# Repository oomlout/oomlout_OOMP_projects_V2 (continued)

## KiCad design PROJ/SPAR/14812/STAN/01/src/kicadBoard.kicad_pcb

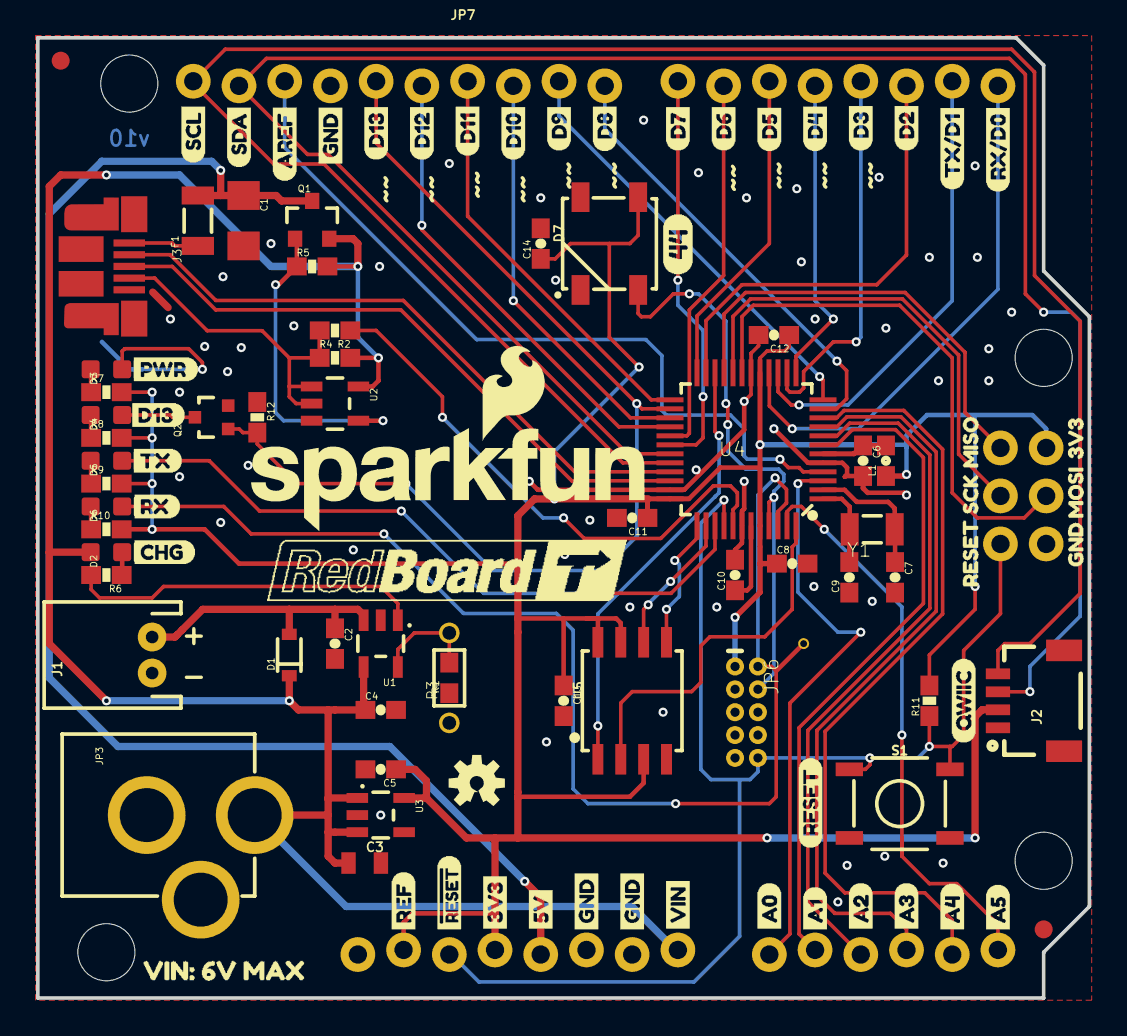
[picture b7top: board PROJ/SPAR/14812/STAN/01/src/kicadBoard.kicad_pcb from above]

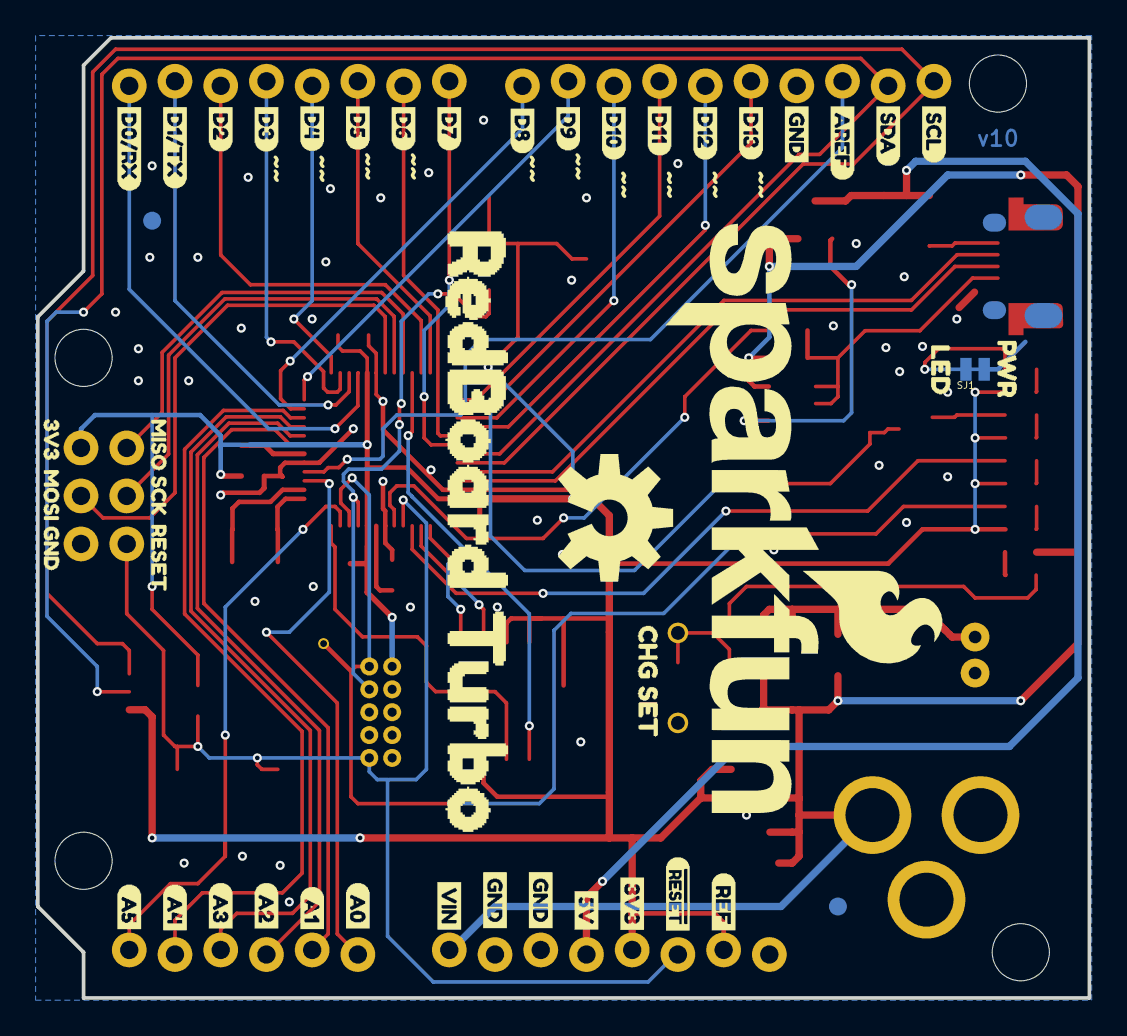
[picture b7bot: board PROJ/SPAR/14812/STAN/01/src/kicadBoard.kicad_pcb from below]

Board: 2 copper layers, 58.4 x 53.3 mm, 149 parts (46 on the bottom side), 58 nets.

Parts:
C1: 2.2UF; 1206@1
C2, C4: 4.7uF; 0603-CAP
C3: 1.0uF; 0805
C5: 2.2uF; 0603-CAP
C6, C8, C10, C11, C12, C13, C14: 0.1uF; 0603-CAP
C7, C9: 15pF; 0603-CAP
D1: BAT20J; SOD-323
D2, D6: Yellow; LED-0603
D3: RED; LED-0603
D4: BLUE; LED-0603
D5: GREEN; LED-0603
D7: WS2812B
F1: 500mA; PTC-1206
FID1, FID2, FID3, FID4: FIDUCIAL1X2; FIDUCIAL-1X2
FRAME1: FRAME-LEDGER; CREATIVE_COMMONS
J1: JST-2-PTH
J2: 1X04_1MM_RA
J3: USB-MICROB-PTH-MILL
JP3: POWER_JACKPTH; POWER_JACK_PTH
JP6: CORTEX_DEBUGPTH; 2X5-PTH-1.27MM
JP7: ARDUINO_UNO_R3LOCK_HOLES; ARDUINO_R3_LOCK_HOLES
L1: FB - 30Ohm; 0603
LOGO1: SFE_LOGO_NAME_FLAME.2_INCH; SFE_LOGO_NAME_FLAME_.2
LOGO2: SFE_LOGO_NAME_FLAME.3_INCH; SFE_LOGO_NAME_FLAME_.3
LOGO3: OSHW-LOGOS; OSHW-LOGO-S
LOGO4: OSHW-LOGOL; OSHW-LOGO-L
Q1: 2.5A/30V; SOT23-3
Q2: 2N7002PW; SOT323
R1: 3.9K; 0603
R2, R6, R7, R8, R9, R10: 330; 0603-RES
R3: PROG; 1_6W-RES
R4, R12: 100k; 0603-RES
R5: 47K; 0603-RES
R11: 10K; 0603-RES
S1: TACTILE_SWITCH_SMD_5.2MM
SJ1: PWR-LED; PAD-JUMPER-2-NC_BY_TRACE_NO_SILK
TP1: TEST-POINTTP_15TH_THRU; TP_15TH
U1: MCP73831; SOT23-5
U2: 74AHC1G125; SOT23-5
U3: 3.3V; SOT23-5
U4: ATSAMD21G-A; TQFP-48
U5: W25Q32FV; SOIC-8
U$1, U$44: #RESET1
U$2: 3V317
U$3: 5V18
U$4: CHG30
U$5: RX#D015
U$6: TX#D114
U$7: D213
U$8: D312
U$9: D411
U$10: D510
U$11: D69
U$12: D78
U$13: D87
U$14: D96
U$15: D105
U$16: D114
U$17: D123
U$18: D132
U$19, U$36, U$37: GND16
U$20, U$81: SDA1
U$21, U$80: SCL0
U$22: TX28
U$23: RX29
U$24: PWR26
U$25: D1327
U$26: REF0
U$27, U$53: AREF2
U$28: QWIIC31
U$29: A020
U$30: A121
U$31: A222
U$32: A323
U$33: A424
U$34: A525
U$35: VIN19
U$38: GND7
U$39: MOSI4
U$40: 3V36
U$41: SCK5
U$42: MISO3
U$43, U$83: RESET0
U$45: 3V325
U$46: 3V30
U$47: A018
U$48: A119
U$49: A220
U$50: A321
U$51: A422
U$52: A523
U$54: LED1
U$55: D0#RX17
U$56: D1#TX15
U$57: 5V26
U$58: D79
U$59: D88
U$60: D97
U$61: D106
U$62: D115
U$63: D124
U$64: D133
U$65: D214
U$66: D313
U$67: D412
U$68: D511
U$69: D610
U$70, U$71, U$72: GND24
U$73: GND33
U$74: PWR0
U$75: MISO30
U$76: MOSI34
U$77: REF28
U$78: RESET32
U$79: SCK31
U$82: VIN27
U$84: 440
U$85: REDBOARD_TURBO1
U$86: BITMAP#JPG
U$87: CHG_SET1
U$88: VIN#_6V_MAX2
Y1: 32.768kHz; CRYSTAL-SMD-3.2X1.5MM

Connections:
3.3V: C5.1, C8.1, C11.1, C12.1, C13.1, C14.1, D7.1, J2.2, JP6.1, JP7.3.3V, JP7.IOREF, JP7.VCC, L1.1, R7.2, R8.2, R9.2, R10.2, R11.2, U3.5, U4.17, U4.36, U4.44, U5.3, U5.7, U5.8
A0: JP7.A0, U4.3
A1: JP7.A1, U4.7
A2: JP7.A2, U4.8
A3: JP7.A3, U4.9
A4: JP7.A4, U4.10
A5: JP7.A5, U4.47
AREF: JP7.AREF, U4.4
CHG_STAT: R6.2, U1.1
D0/RXI: JP7.D0, U4.16
D1/TXO: JP7.D1, U4.15
D2: JP7.D2, U4.23
D3: JP7.D3, U4.14
D4: JP7.D4, U4.13
D5: JP7.D5, U4.24
D6: JP7.D6, U4.29
D7: JP7.D7, U4.30
D8: JP7.D8, U4.11
D9: JP7.D9, U4.12
D10: JP7.D10, U4.27
D11: JP7.D11, U4.25
D12: JP7.D12, U4.28
D13: JP7.D13, Q2.1, R12.2, U4.26
FLASH_CS: U4.22, U5.1
FLASH_MISO: U4.48, U5.2
FLASH_MOSI: U4.37, U5.5
FLASH_SCK: U4.38, U5.6
GND: C1.2, C2.2, C3.2, C4.2, C5.2, C6.2, C7.2, C8.2, C9.1, C10.2, C11.2, C12.2, C13.2, C14.2, D7.3, J1.1, J2.1, J3.GND, J3.SHIELD, J3.SHIELD2, J3.SHIELD3, J3.SHIELD4, J3.SHIELD5, J3.SHIELD6, J3.SHIELD7, J3.SHIELD8, J3.SHIELD9, J3.SHIELD10, JP3.GND, JP3.GNDBREAK, JP6.3, JP6.5, JP7.GND@1, JP7.GND@2, JP7.GND@3, JP7.GND@4, Q2.2, R1.1, R3.1, R12.1, S1.3, S1.4, SJ1.1, U1.2, U2.3, U3.2, U4.5, U4.18, U4.35, U4.42, U5.4
LED/SWCLK: D7.4, JP6.4, U4.45
unnamed: F1.1, J3.VBUS
unnamed: C9.2, U4.1, Y1.P$2
unnamed: D4.C, Q2.3
unnamed: C7.1, U4.2, Y1.P$1
unnamed: D3.A, R7.1
unnamed: D4.A, R8.1
unnamed: D2.C, R6.1
unnamed: D5.A, R9.1
unnamed: D6.A, R10.1
unnamed: D3.C, SJ1.2
unnamed: R1.2, R3.2, U1.5
RX_LED/SWDIO: D6.C, JP6.2, TP1.P$1, U4.46
SCL: J2.4, JP7.SCL, U4.32
SDA: J2.3, JP7.SDA, U4.31
SPI_MISO: JP7.MISO, U4.21
SPI_MOSI: JP7.MOSI, U4.19
SPI_SCK: JP7.SCK, U4.20
TX_LED: D5.C, U4.39
USB_D+: J3.D+, U4.34
USB_D-: J3.D-, U4.33
USB_HOST_EN: R2.1, U4.41
USB_HOST_POWER_EN: Q1.1, R5.1, U2.4
USB_ID: J3.ID, R2.2, R4.1, U2.1, U2.2
VBAT: C2.1, D1.A, J1.2, U1.3
VDDANA: C6.1, L1.2, U4.6
VDDCORE: C10.1, U4.43
VIN: C3.1, C4.1, D1.C, D2.A, JP3.PWR, JP7.VIN, Q1.2, R4.2, R5.2, U1.4, U2.5, U3.1, U3.3
VUSB: C1.1, F1.2, JP7.5V, Q1.3
~RESET: JP6.10, JP7.RESET@1, JP7.RESET@2, R11.1, S1.1, S1.2, U4.40

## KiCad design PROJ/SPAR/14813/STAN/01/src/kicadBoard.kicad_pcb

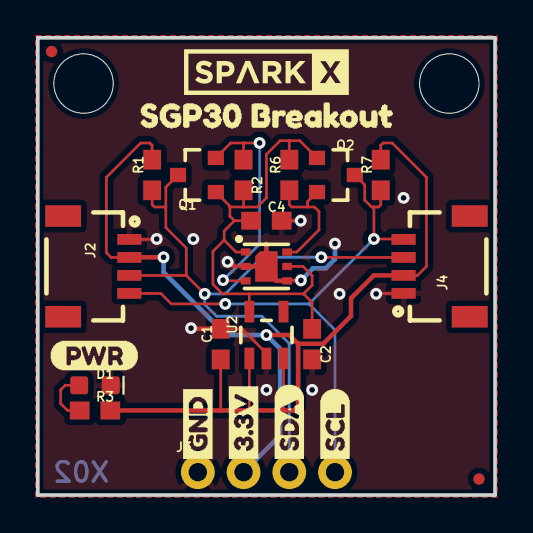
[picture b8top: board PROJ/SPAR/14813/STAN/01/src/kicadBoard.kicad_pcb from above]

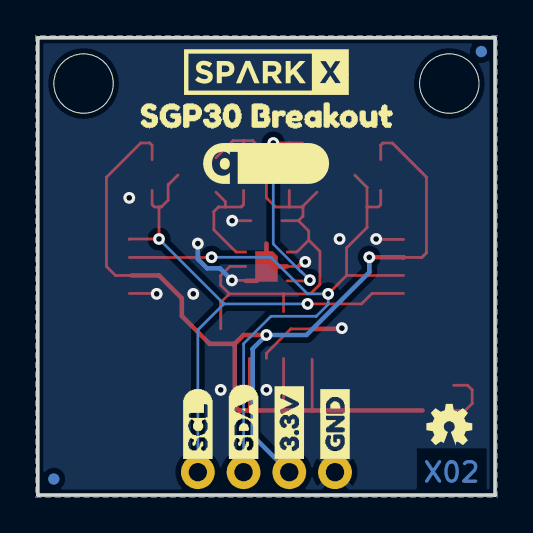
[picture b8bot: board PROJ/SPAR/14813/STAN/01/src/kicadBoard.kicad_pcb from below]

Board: 2 copper layers, 25.4 x 25.4 mm, 38 parts (10 on the bottom side), 8 nets.

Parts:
C1, C2: 1.0uF; 0603
C4: 0.1uF; 0603
D1: RED; LED-0603
FRAME1: FRAME-LETTER; CREATIVE_COMMONS
J2, J4: 1X04_1MM_RA
J3: PTH; 1X04_NO_SILK
JP1, JP2, JP5, JP6: FIDUCIALUFIDUCIAL; MICRO-FIDUCIAL
JP3, JP4: STAND-OFF
LOGO1: OSHW-LOGOMINI; OSHW-LOGO-MINI
Q1, Q2: SOT23-3
R1, R2, R6, R7: 10k; 0603
R3: 1k; 0603
U1: SGP30
U2: AP2112k; SOT23-5
U$1, U$2: SPARKX-LOGO4; SPARKX-MEDIUM
U$3, U$22: GND1
U$4, U$21: 3#3V2
U$5, U$27: SDA8
U$6, U$26: SCL9
U$7, U$8: SGP30_BREAKOUT1
U$9: QWIIC_LOGO_7MM; QWIIC_7MM
U$10: (PWR)

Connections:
1.8V: C2.1, C4.1, Q1.1, Q2.1, R2.2, R6.2, U1.1, U1.5, U2.5
3.3V: C1.1, J2.2, J3.2, J4.2, R1.2, R3.2, R7.2, U2.1, U2.3
GND: C1.2, C2.2, C4.2, D1.C, J2.1, J3.1, J4.1, U1.2, U1.4, U1.DIEPAD, U2.2
LSCL: Q2.2, R6.1, U1.6
LSDA: Q1.2, R2.1, U1.3
unnamed: D1.A, R3.1
SCL: J2.4, J3.4, J4.4, Q2.3, R7.1
SDA: J2.3, J3.3, J4.3, Q1.3, R1.1
